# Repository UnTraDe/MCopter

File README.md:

# MCopter

A quadcopter built from scratch.

Currently there is a working PCB for the flight controller + basic firmware.

### Working (kind-of) features--

* Simple PID flight stabilization
* Radio communication via external radio module (both controlling the copter and sending telemtry data to the controller
* Simple remote controller made out of an old RC toy radio + arduino pro mini + nRF24

### Planned

* Designing custom frame and 3D print it
* Using an embedded radio solution (probably nRF24 based)
* Using 9-axis fusion instead of 6-axis to avoid yaw drift.

# The Hardware

This is version 2.0 of the flight controller PCB.
The PCB is design with 2 layers to keep down the cost, in the future I might redesign it with 4 layers to make it smaller. I'm also using 0805 to allow for easy hand-soldering.

The microcontroller is STM32F410RBT, a powerful 32-bit ARM Cortex M4 with hardware floating point unit and a lot of useful peripherals.

Other major components (sensors):

* ICM-20689; MEMES gyroscope + accelerometer. This is the newer generation of the popular MPU-6050 used in a lot of commercial flight controllers.
* MAG3110; A magnetometer.
* MS5637; A Barometer

The ICM-20689 togheter with the MAG3110 can be used for 9-axis fusion to provide better heading, avoid yaw drifting and togheter with the barometer also have an height based control instead of throttle based one.

* TODO take a better picture...

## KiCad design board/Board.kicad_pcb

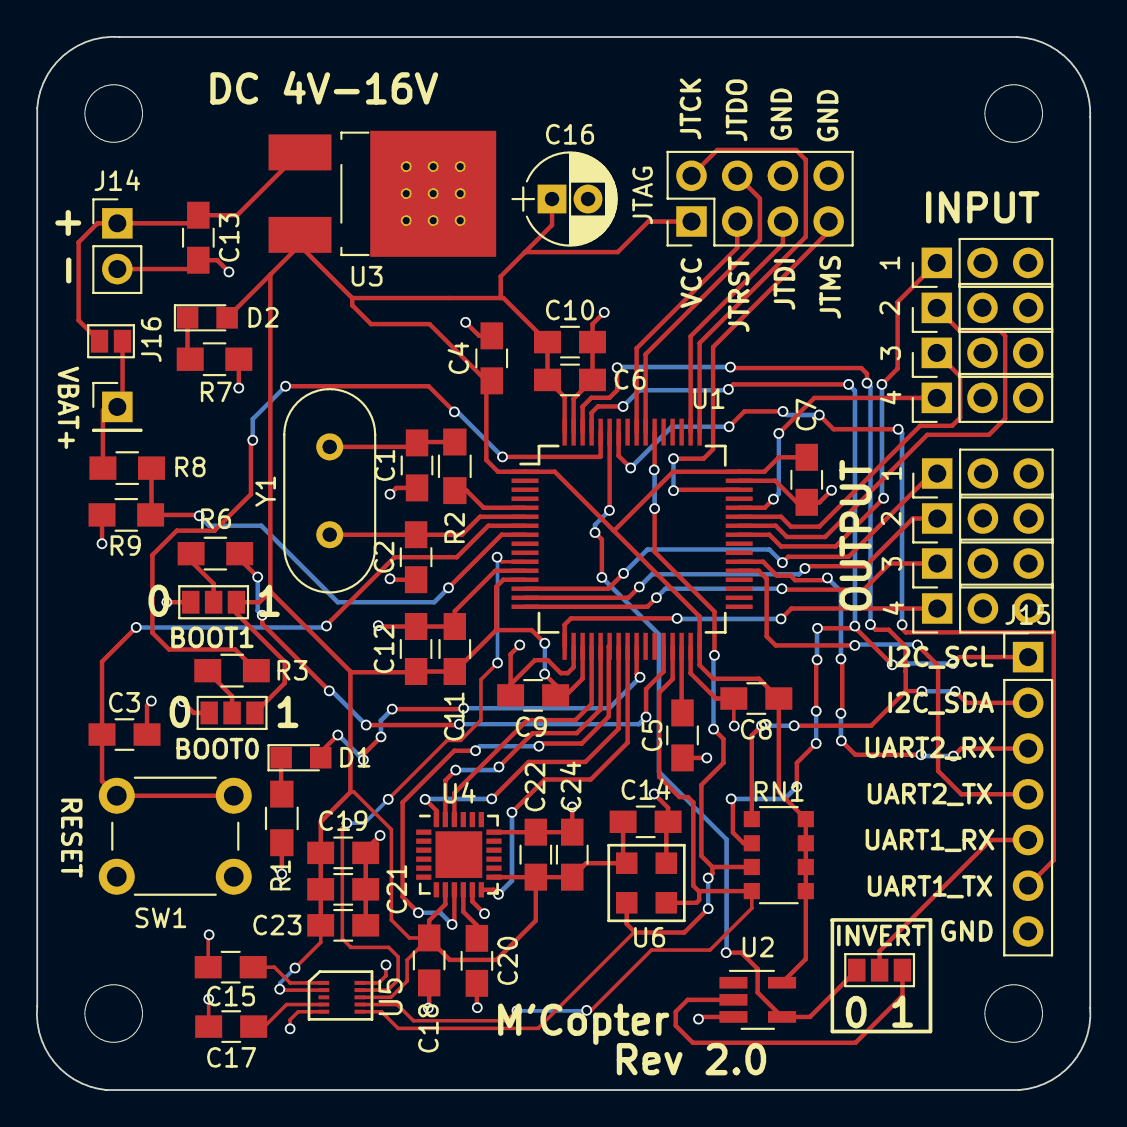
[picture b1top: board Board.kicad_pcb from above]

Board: 2 copper layers, 58.5 x 58.5 mm, 54 parts (0 on the bottom side), 45 nets.

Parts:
1, 1#2, 2, 2#2, 3, 3#2, 4, 4#2: CONN_01X03; Pin_Header_Straight_1x03_Pitch2.54mm
C1, C2: 20pF; C_0805_HandSoldering
C3, C4, C6, C7, C8, C9, C12, C14, C15, C17, C21, C23, C24: 100nF; C_0805_HandSoldering
C5, C10: 4.7uF; C_0805_HandSoldering
C11, C19: 1uF; C_0805_HandSoldering
C13: 0.1uF; C_0805_HandSoldering
C16: 2.2uF; CP_Radial_D5.0mm_P2.00mm
C18: 10nF; C_0805_HandSoldering
C20: 0.47uF; C_0805_HandSoldering
C22: 2.2uF; C_0805_HandSoldering
D1, D2: LED; LED_0805
J14: CONN_01X02; Pin_Header_Straight_1x02_Pitch2.54mm
J15: CONN_01X07; Pin_Header_Straight_1x07_Pitch2.54mm
J16: GS2
JTAG: CONN_02X04; Pin_Header_Straight_2x04_Pitch2.54mm
R1: 22; R_0805_HandSoldering
R2: 0; R_0805_HandSoldering
R3, R6: 10K; R_0805_HandSoldering
R7: 220; R_0805_HandSoldering
R8: 62K; R_0805_HandSoldering
R9: 22K; R_0805_HandSoldering
RN1: 4.7K; R_Array_Convex_4x1206
SW1: SW_Push; SW_PUSH_6mm
U1: STM32F410RBTx; LQFP-64_10x10mm_Pitch0.5mm_handsoldering
U2: SN74LVC1G04; SOT-23-5_HandSoldering
U3: LF33ABDT-TR; TO-252-2Lead
U4: ICM-20689; QFN-24-1EP_4x4mm_Pitch0.5mm
U5: MAG3110; DFN_2x2mm_10pin_0.4pitch
U6: MS5637
Y1: 25 MHz; Crystal_HC49-U_Vertical

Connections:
+BATT: C13.1, J14.1, J16.1, U3.1
BATT_ADC: R8.2, R9.1, U1.8
GND: 1.3, 1#2.3, 2.3, 2#2.3, 3.3, 3#2.3, 4.3, 4#2.3, C1.1, C2.1, C3.2, C4.2, C5.2, C6.2, C7.2, C8.2, C9.2, C10.2, C11.2, C12.2, C13.2, C14.2, C15.2, C16.2, C17.2, C18.2, C19.2, C20.2, C21.2, C22.2, C23.2, C24.2, J14.2, J15.7, JTAG.6, JTAG.8, R1.2, R7.2, R9.2, SW1.1, U1.12, U1.18, U1.31, U1.47, U1.63, U2.3, U3.2, U4.11, U4.18, U5.5, U5.10, U6.4
I2C1_SCL: J15.1, RN1.2, U1.61
I2C1_SDA: J15.2, RN1.1, U1.62
I2C2_SCL: RN1.4, U1.29, U5.7, U6.3
I2C2_SDA: RN1.3, U1.54, U5.6, U6.2
ICM_INT: U1.24, U4.12
ICM_SPI_CS: U1.20, U4.22
ICM_SPI_MISO: U1.22, U4.9
ICM_SPI_MOSI: U1.23, U4.24
ICM_SPI_SCK: U1.21, U4.23
JTCK: JTAG.2, U1.49
JTDI: JTAG.5, U1.50
JTDO: JTAG.4, U1.55
JTMS: JTAG.7, U1.46
JTRST: JTAG.3, U1.56
MAG_INT: U1.11, U5.9
unnamed: C1.2, R2.1, Y1.2
unnamed: C2.2, U1.6, Y1.1
unnamed: C3.1, SW1.2, U1.7
unnamed: C5.1, U1.30
unnamed: C15.1, U5.1
unnamed: C17.1, U5.4
unnamed: C20.1, U4.10
unnamed: D1.1, R1.1
unnamed: D1.2, U1.25
unnamed: D2.1, R7.1
unnamed: J16.2, R8.1
unnamed: R2.2, U1.5
unnamed: R3.2, U1.60
unnamed: R6.1, U1.28
PWM_INPUT_1: 1#2.1, U1.41
PWM_INPUT_2: 2#2.1, U1.42
PWM_INPUT_3: 3#2.1, U1.43
PWM_INPUT_4: 4#2.1, U1.44
PWM_OUTPUT_1: 1.1, U1.14
PWM_OUTPUT_2: 2.1, U1.15
PWM_OUTPUT_3: 3.1, U1.16
PWM_OUTPUT_4: 4.1, U1.17
UART1_RX: U1.59, U2.4
UART1_TX: J15.6, U1.58
UART2_RX: J15.3, U1.38
UART2_TX: J15.4, U1.37
VCC: C4.1, C6.1, C7.1, C8.1, C9.1, C10.1, C11.1, C12.1, C14.1, C16.1, C18.1, C19.1, C21.1, C22.1, C23.1, C24.1, D2.2, JTAG.1, RN1.5, RN1.6, RN1.7, RN1.8, U1.1, U1.13, U1.19, U1.32, U1.48, U1.64, U2.5, U3.3, U4.8, U4.13, U5.2, U5.8, U6.1

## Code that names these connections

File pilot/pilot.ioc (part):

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Mcu.Name=STM32F410R(8-B)Tx
Mcu.Package=LQFP64
Mcu.UserName=STM32F410RBTx
PA0-WKUP.Signal=S_TIM5_CH1
PA1.Signal=S_TIM5_CH2
PA10.Signal=S_TIM1_CH3
PA11.Signal=S_TIM1_CH4
PA13.Mode=JTAG_5_pins
PA13.Signal=SYS_JTMS-SWDIO
PA14.Mode=JTAG_5_pins
PA14.Signal=SYS_JTCK-SWCLK
PA15.Mode=JTAG_5_pins
PA15.Signal=SYS_JTDI
PA2.Signal=S_TIM5_CH3
PA3.Signal=S_TIM5_CH4
PA4.Signal=GPIO_Output
PA5.Mode=Full_Duplex_Master
PA5.Signal=SPI1_SCK
PA6.Mode=Full_Duplex_Master
PA6.Signal=SPI1_MISO
PA7.Mode=Full_Duplex_Master
PA7.Signal=SPI1_MOSI
PA8.Signal=S_TIM1_CH1
PA9.Signal=S_TIM1_CH2
PB10.Mode=I2C
PB10.Signal=I2C2_SCL
PB11.Mode=I2C
PB11.Signal=I2C2_SDA
PB12.Signal=GPIO_Output
PB13.Mode=Full_Duplex_Master
PB13.Signal=SPI2_SCK
PB14.Mode=Full_Duplex_Master
PB14.Signal=SPI2_MISO
PB15.Mode=Full_Duplex_Master
PB15.Signal=SPI2_MOSI
PB3.Mode=JTAG_5_pins
PB3.Signal=SYS_JTDO-SWO
PB4.Mode=JTAG_5_pins
PB4.Signal=SYS_JTRST
PB6.Mode=Asynchronous
PB6.Signal=USART1_TX
PB7.Mode=Asynchronous
PB7.Signal=USART1_RX
PB8.Mode=I2C
PB8.Signal=I2C1_SCL
PB9.Mode=I2C
PB9.Signal=I2C1_SDA
PC0.Signal=ADCx_IN10
PC4.Signal=GPXTI4
PC5.Signal=GPIO_Output
PC6.Mode=Asynchronous
PC6.Signal=USART6_TX
PC7.Mode=Asynchronous
PC7.Signal=USART6_RX
PH0\ -\ OSC_IN.Mode=HSE-External-Oscillator
PH0\ -\ OSC_IN.Signal=RCC_OSC_IN
PH1\ -\ OSC_OUT.Mode=HSE-External-Oscillator
PH1\ -\ OSC_OUT.Signal=RCC_OSC_OUT
RCC.HSE_VALUE=25000000
RCC.SYSCLKFreq_VALUE=100000000
RCC.SYSCLKSource=RCC_SYSCLKSOURCE_PLLCLK
board=pilot

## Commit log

2017-04-17 regenerated project to fit new folder structure
2017-04-17 removed comments
2017-04-17 configure timers
2017-04-17 completed motors
2017-04-17 now handles float
2017-04-17 connected PID loop
2017-04-17 work in progresS
2017-04-17 appearntly those comments were importatnt...
2017-04-17 ehhh
2017-04-17 reading SBUS with DMA
2017-04-18 uart signal inverter; battery measurement
2017-04-18 inverter gate is now optional
2017-04-18 pcb rev2, work in progress
2017-04-19 removed GPIO headers
2017-04-19 added MS5611 component
2017-04-19 added mag 3110 component
2017-04-20 replaced barometer
2017-04-20 decouple cap
2017-04-20 smaller JTAG pin
2017-04-20 removed NRST global labl
2017-04-20 new pcb
2017-04-20 handsoldering lqfp
2017-04-21 assigned the new footprint
2017-04-21 organized the board a bit
2017-04-21 forgot to rename this function
2017-04-21 semphore/mutex?
2017-04-21 ready for first flight?
2017-04-22 misc fixes
2017-04-23 a bit more order
2017-04-23 using resistor array for I2C pullups
2017-04-23 put everything togheter
2017-04-23 50x50mm
2017-04-24 rounded corners
2017-04-24 mounting holes
2017-04-24 a bit of reorganization
2017-04-24 started routing
2017-04-24 more routes
2017-04-24 backup
2017-04-24 outing mag
2017-04-24 finished routing
2017-04-24 moved some floating vias
2017-04-24 via stiching?
2017-04-24 added via stiching
2017-04-24 exposed another UART
2017-04-24 silk screen items
2017-04-25 input/output silkscreen
2017-04-25 silkscreen
2017-04-25 fixed a few unconnected pads
2017-04-25 more silkscreen
2017-04-25 moved a bit more silkscreen
2017-04-25 vs2017?
2017-04-25 oneshot125git add -Agit add -A
2017-04-25 added comments
2017-04-29 back to using PWM because OneShot125 had some problem with implementation
2017-04-29 forgot this
2017-04-29 sync sbus
2017-04-29 failsafe
2017-04-29 calibration
2017-04-29 calculating accel and gyro bias
2017-04-30 applying accel and gyro biases locally
2017-05-01 using different UART for debugging
2017-05-01 enable RX too
2017-05-01 moved calibrate to a different function
2017-05-01 removed temp file
2017-05-01 dont include this file next time...
2017-05-01 removed unused register definitions
2017-05-01 removed comment
2017-05-01 back to using regular mode instead of DMA for UART6
2017-05-01 uncomment this
2017-05-01 seperated calibrate and eeprom
2017-05-01 storing the biases in code (temp)
2017-05-09 reading baro data with I2C
2017-05-09 magnetometer I2C test
2017-05-09 I2C fast mode
2017-05-13 added barometer
2017-05-13 added battery voltage monitoring via ADC
2017-05-13 now printing up tp 2 decimal places to minimize UART traffic
2017-05-13 forgot to add this to the ADC commit
2017-05-13 adjusted motor mixxing
2017-05-13 inverter was connected wrong
2017-05-13 fixed inverter connections
2017-05-13 fixed some stupid mistakes, NOW IT FINALLY WORKS
2017-05-13 comment
